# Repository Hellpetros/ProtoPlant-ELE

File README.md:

View this project on [CADLAB.io](https://cadlab.io/project/22799). 

# ProtoPlant-HW

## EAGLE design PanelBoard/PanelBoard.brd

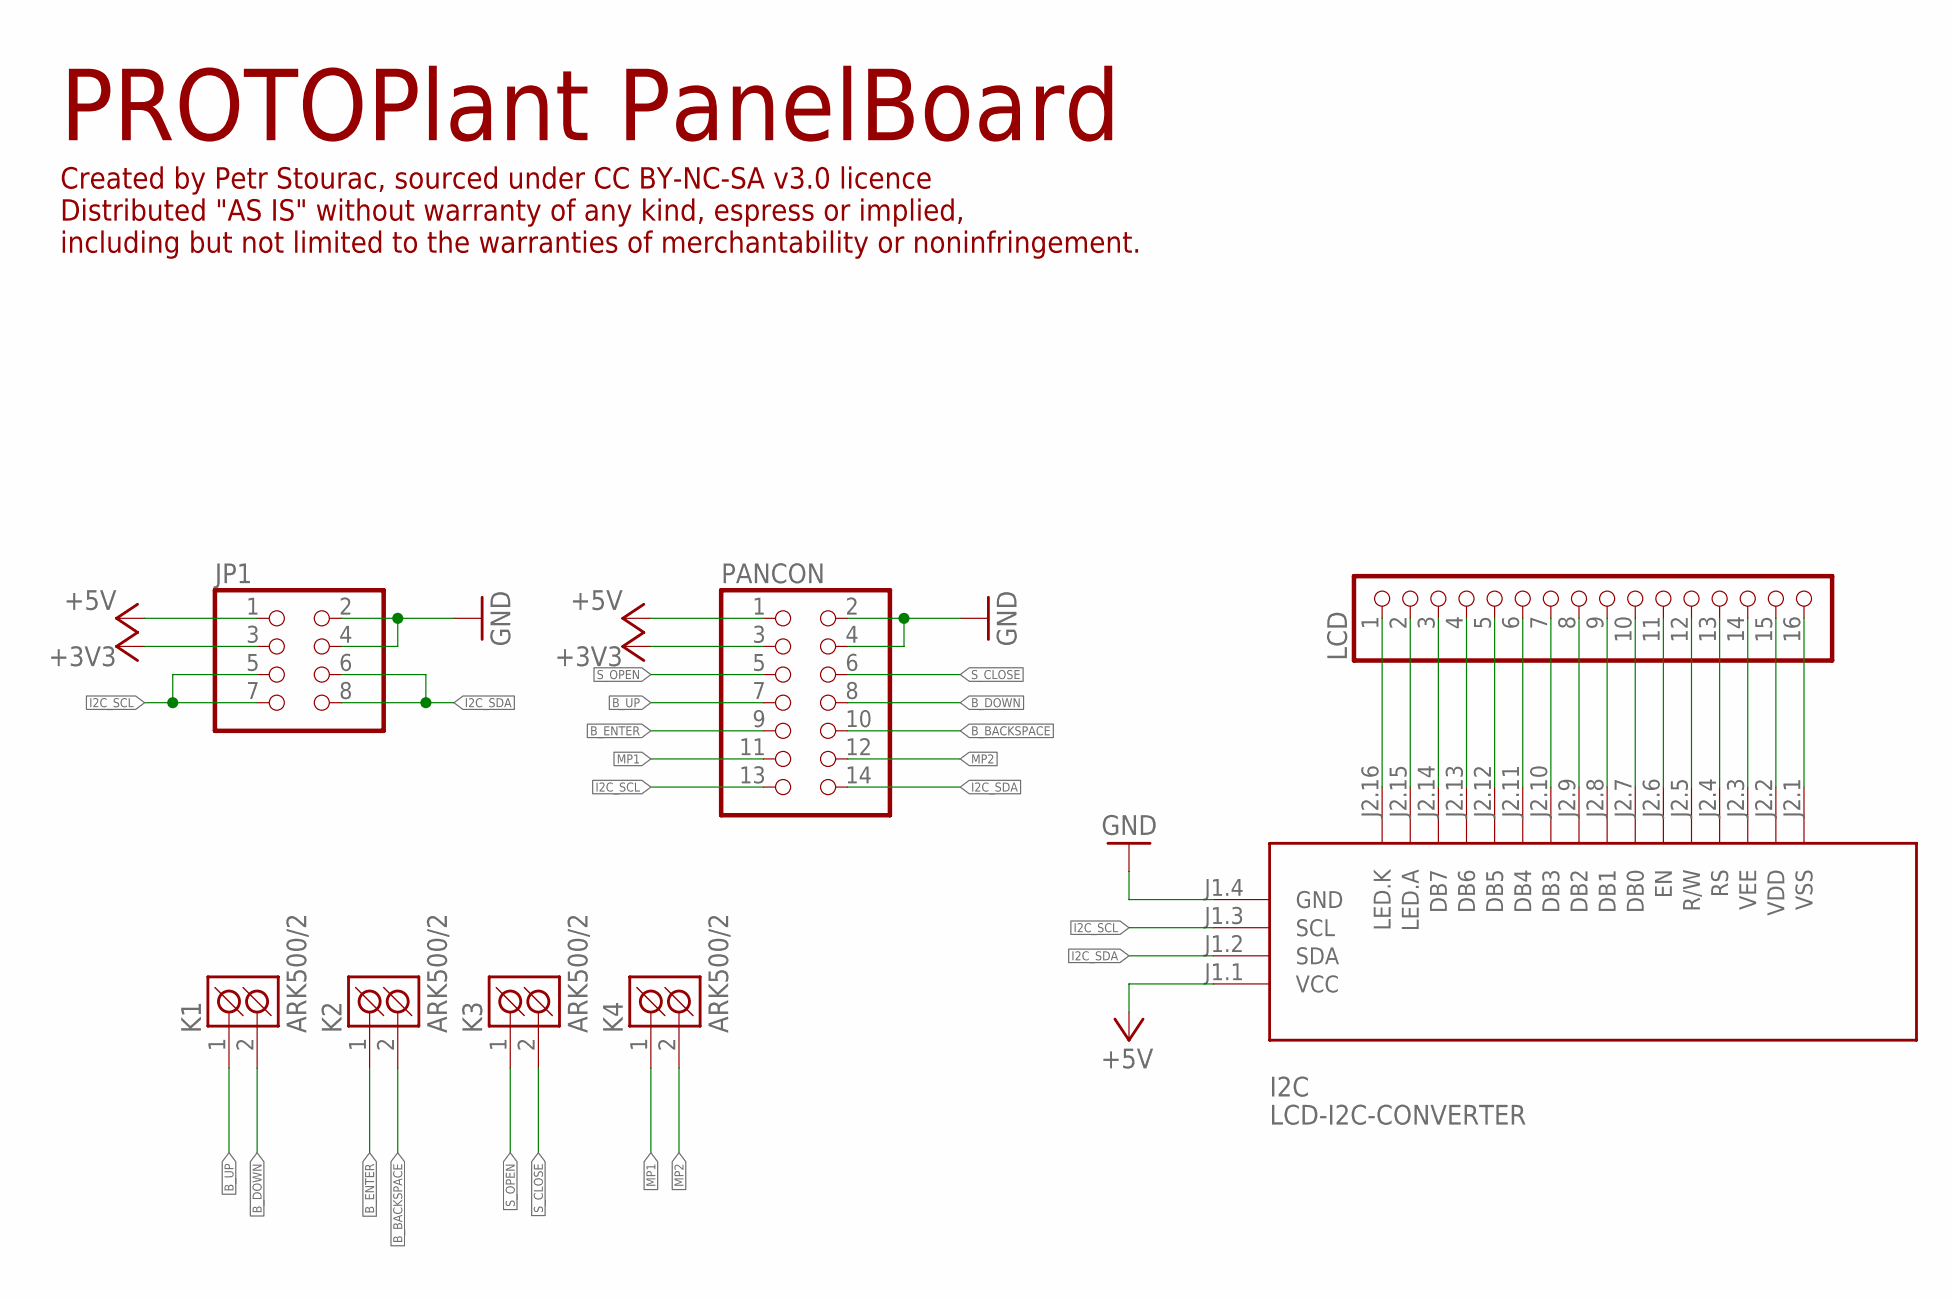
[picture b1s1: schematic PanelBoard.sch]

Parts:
I2C: LCD-I2C-CONVERTER
JP1: PINHD-2X4/90; 2X04/90
K1, K2, K3, K4: ARK500/2
LCD: PINHD-1X16; 1X16
PANCON: PINHD-2X7/90; 2X07/90

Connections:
+3V3: JP1.3, PANCON.3
+5V: I2C.J1.1 (VCC), JP1.1, PANCON.1
B_BACKSPACE: K2.2 (K2), PANCON.10
B_DOWN: K1.2 (K2), PANCON.8
B_ENTER: K2.1 (K1), PANCON.9
B_UP: K1.1 (K1), PANCON.7
GND: I2C.J1.4 (GND), JP1.2, JP1.4, PANCON.2, PANCON.4
I2C_SCL: I2C.J1.3 (SCL), JP1.5, JP1.7, PANCON.13
I2C_SDA: I2C.J1.2 (SDA), JP1.6, JP1.8, PANCON.14
MP1: K4.1 (K1), PANCON.11
MP2: K4.2 (K2), PANCON.12
unnamed: I2C.J2.16 (LED.K), LCD.1
unnamed: I2C.J2.15 (LED.A), LCD.2
unnamed: I2C.J2.14 (DB7), LCD.3
unnamed: I2C.J2.13 (DB6), LCD.4
unnamed: I2C.J2.12 (DB5), LCD.5
unnamed: I2C.J2.11 (DB4), LCD.6
unnamed: I2C.J2.10 (DB3), LCD.7
unnamed: I2C.J2.9 (DB2), LCD.8
unnamed: I2C.J2.8 (DB1), LCD.9
unnamed: I2C.J2.7 (DB0), LCD.10
unnamed: I2C.J2.6 (EN), LCD.11
unnamed: I2C.J2.5 (R/W), LCD.12
unnamed: I2C.J2.4 (RS), LCD.13
unnamed: I2C.J2.3 (VEE), LCD.14
unnamed: I2C.J2.2 (VDD), LCD.15
unnamed: I2C.J2.1 (VSS), LCD.16
S_CLOSE: K3.2 (K2), PANCON.6
S_OPEN: K3.1 (K1), PANCON.5

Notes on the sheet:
PROTOPlant PanelBoard
Created by Petr Stourac, sourced under CC BY-NC-SA v3.0 licence Distributed "AS IS" without warranty of any kind, espress or implied, including but not limited to the warranties of merchantability or noninfringement.

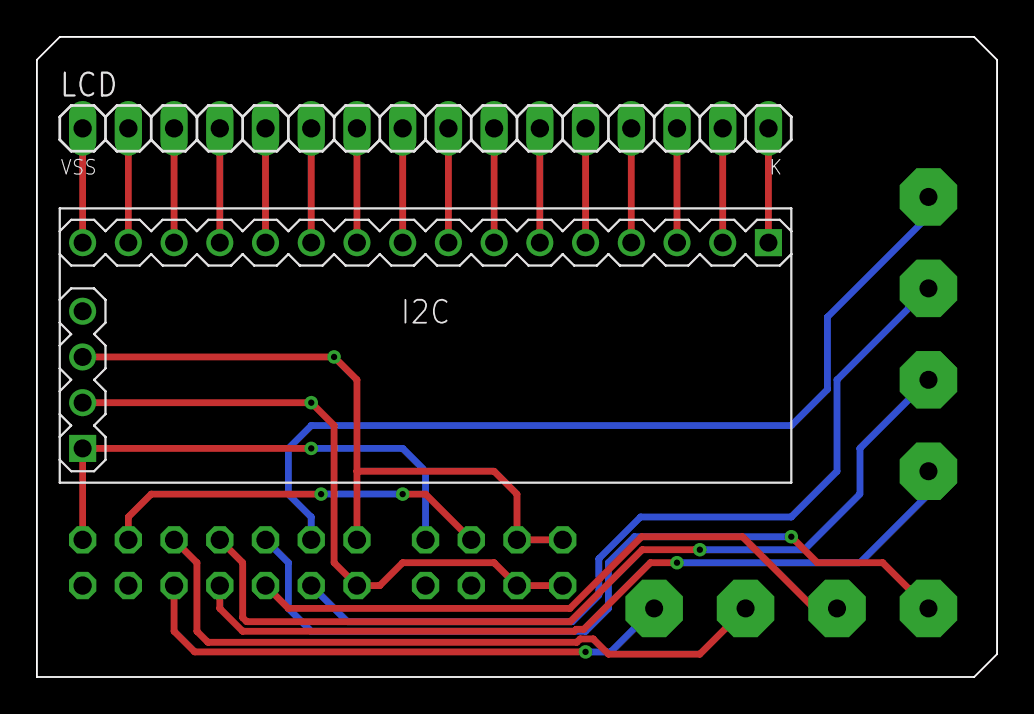
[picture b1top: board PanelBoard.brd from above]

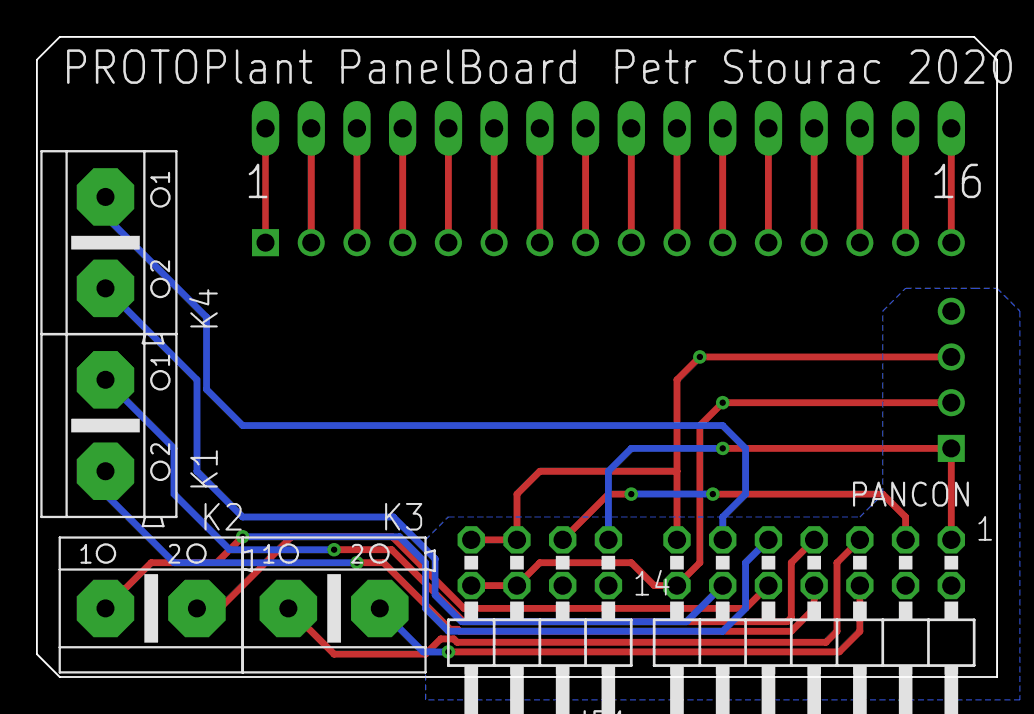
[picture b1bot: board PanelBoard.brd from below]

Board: 2 copper layers, 53.3 x 35.6 mm, 8 parts (6 on the bottom side), 29 nets.

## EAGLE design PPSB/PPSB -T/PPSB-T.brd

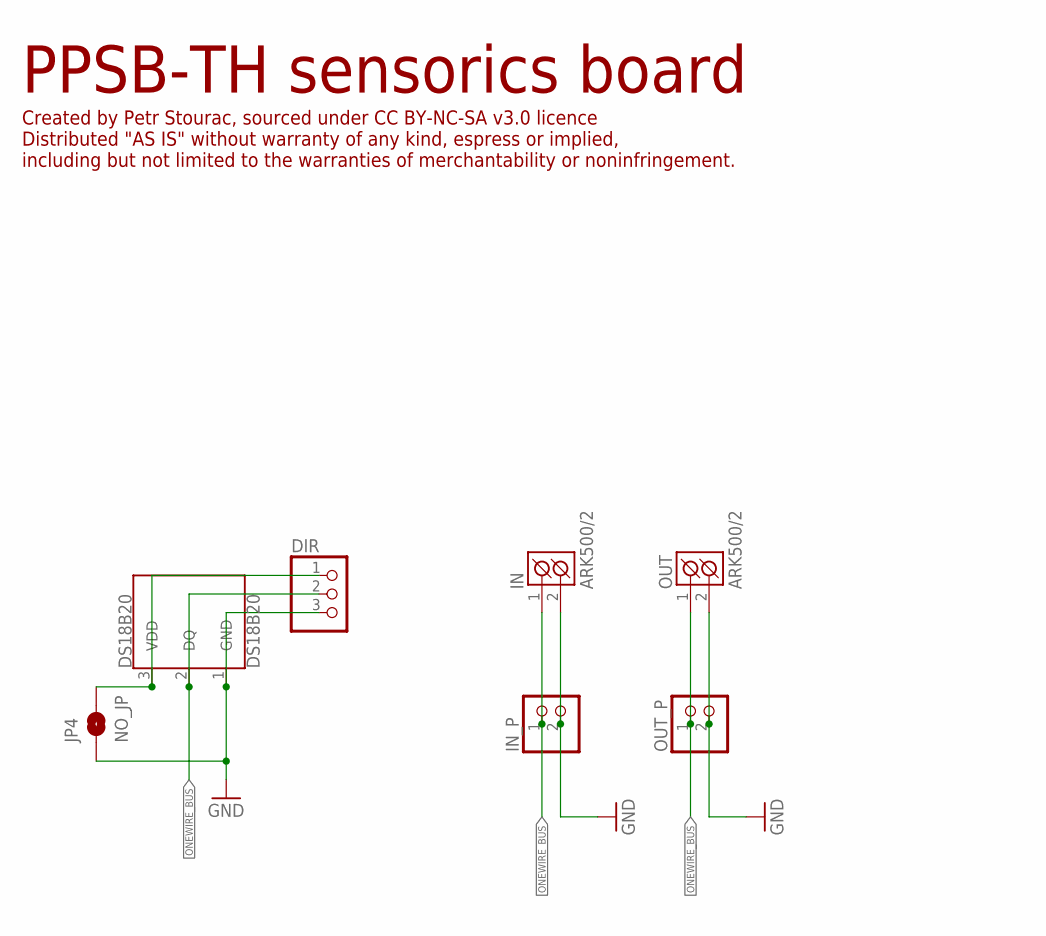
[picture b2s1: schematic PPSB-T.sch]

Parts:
DIR: PINHD-1X3; 1X03
DS18B20: DS18B20; TO-92-AMMO
IN: ARK500/2
IN_P: PINHD-1X2; 1X02
JP4: NO_JP; SMT-JUMPER_2_NO_NO-SILK
OUT: ARK500/2
OUT_P: PINHD-1X2; 1X02

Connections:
GND: DIR.3, DS18B20.1 (GND), IN.2 (K2), IN_P.2, JP4.1, OUT.2 (K2), OUT_P.2
unnamed: DIR.1, DS18B20.3 (VDD), JP4.2
ONEWIRE_BUS: DIR.2, DS18B20.2 (DQ), IN.1 (K1), IN_P.1, OUT.1 (K1), OUT_P.1

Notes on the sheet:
PPSB-TH sensorics board
Created by Petr Stourac, sourced under CC BY-NC-SA v3.0 licence Distributed "AS IS" without warranty of any kind, espress or implied, including but not limited to the warranties of merchantability or noninfringement.

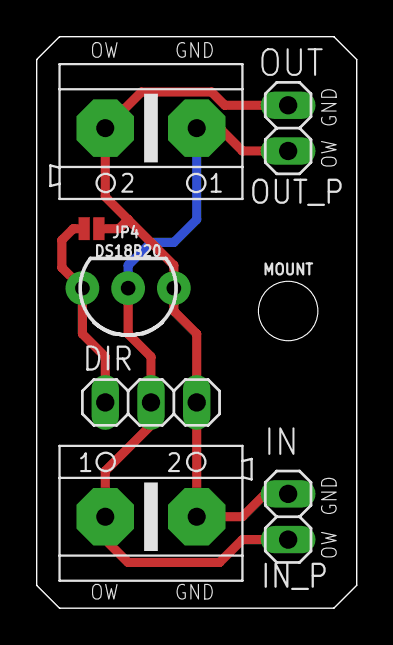
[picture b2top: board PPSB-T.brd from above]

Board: 2 copper layers, 17.8 x 31.8 mm, 8 parts (0 on the bottom side), 3 nets.

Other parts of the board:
MOUNT: STAND-OFF

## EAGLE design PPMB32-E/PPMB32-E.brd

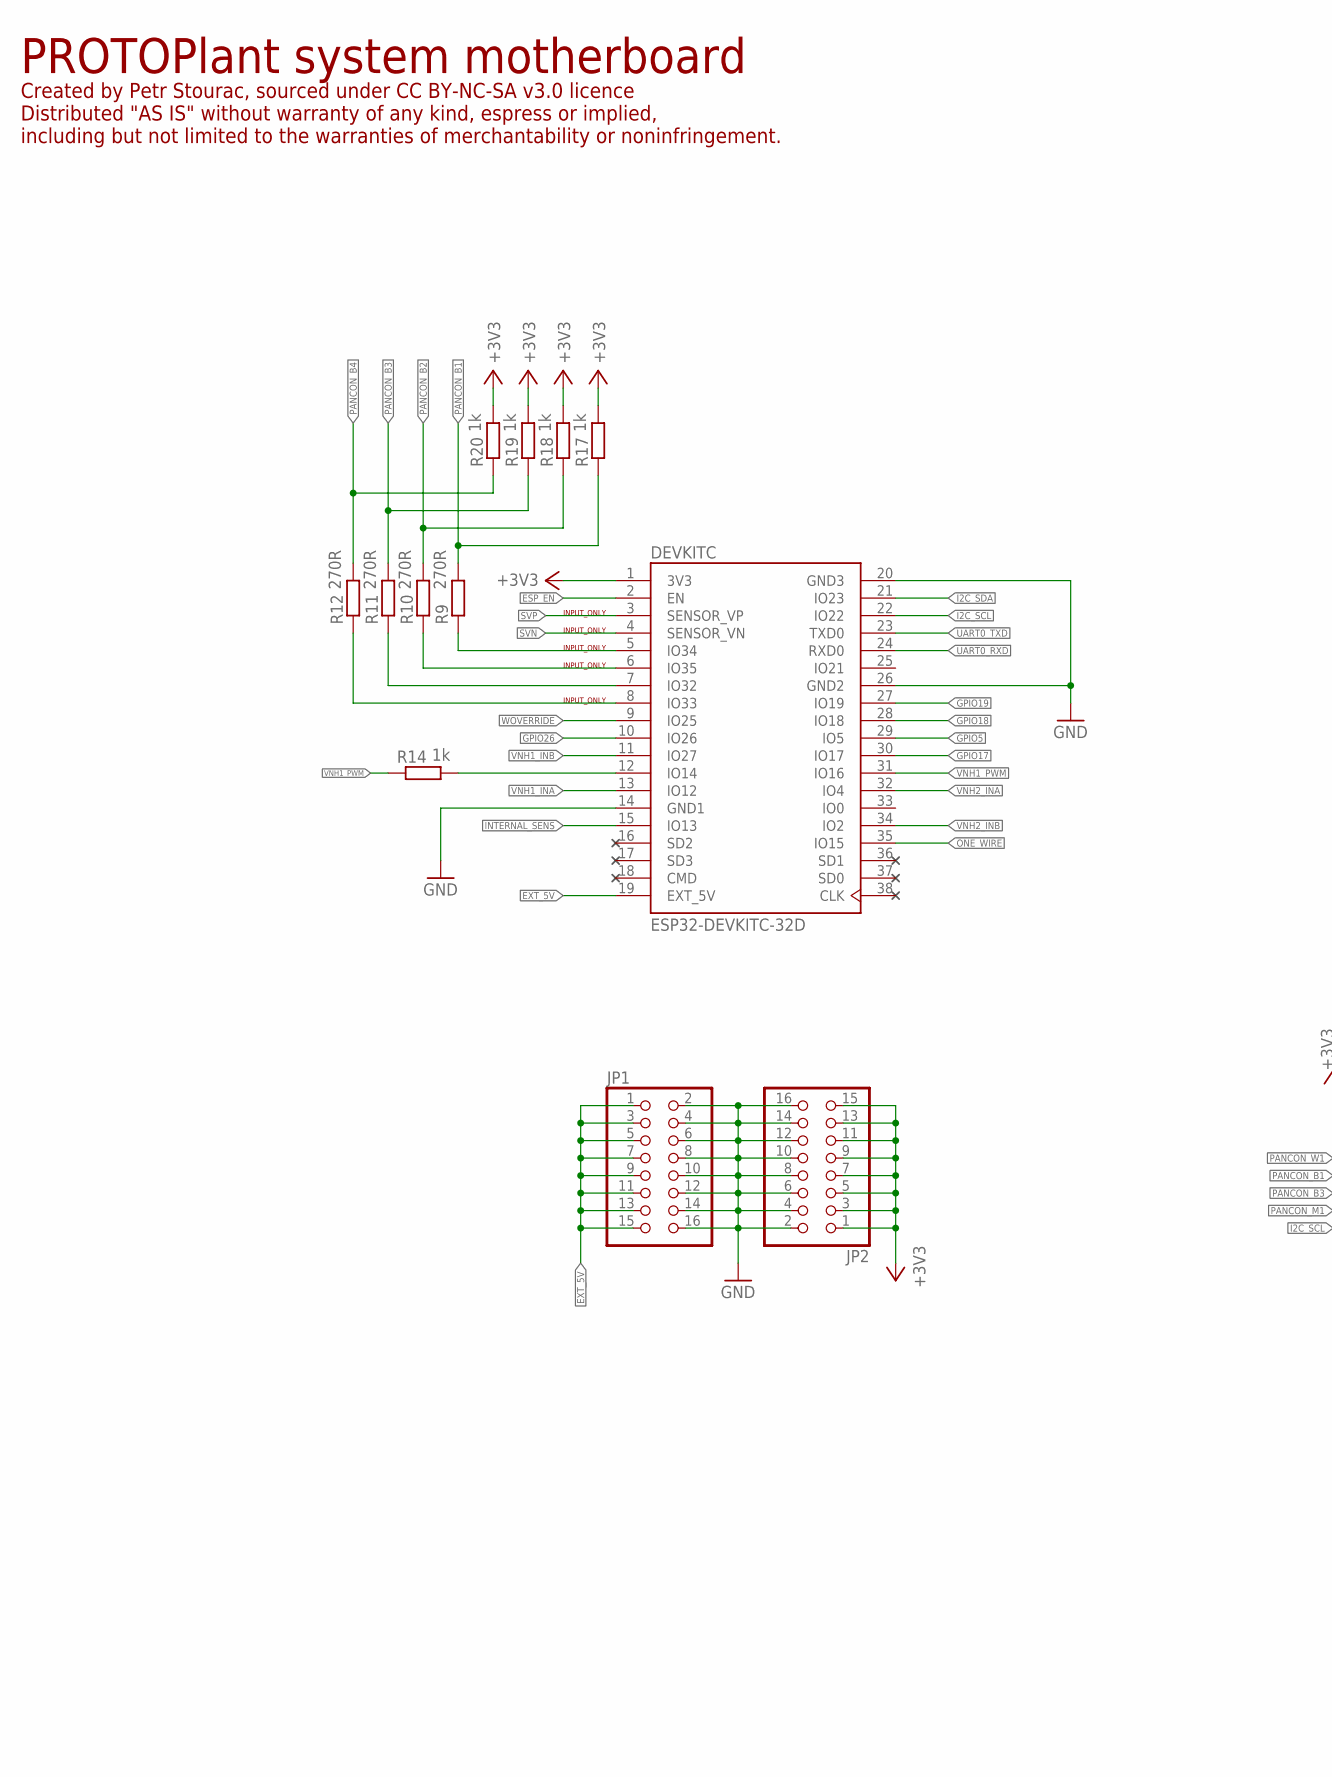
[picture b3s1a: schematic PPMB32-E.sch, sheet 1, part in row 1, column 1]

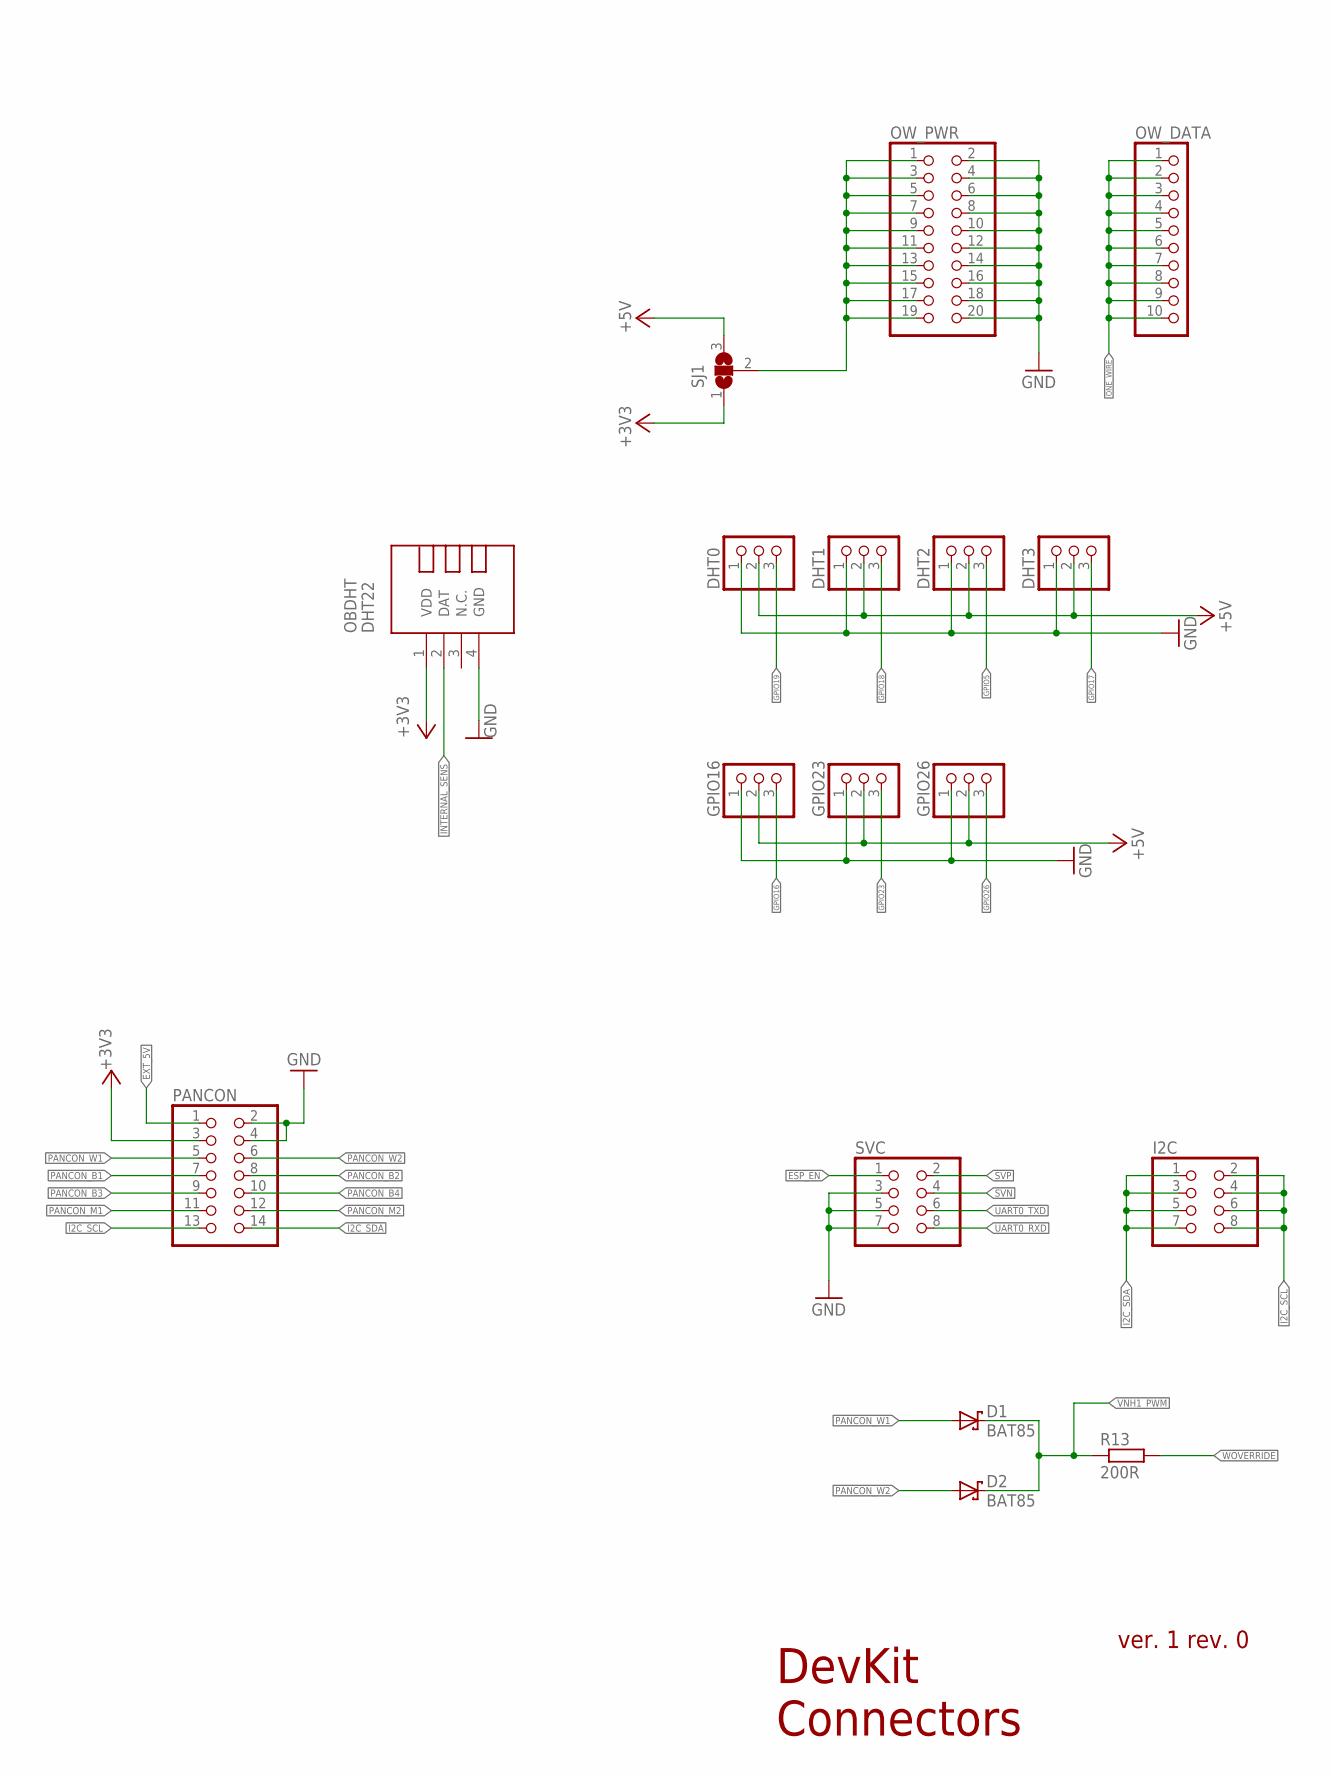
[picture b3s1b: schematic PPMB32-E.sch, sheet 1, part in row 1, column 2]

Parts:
D1, D2: BAT85; DO35-7
DEVKITC: ESP32-DEVKITC-32D; MODULE_ESP32-DEVKITC-32D
DHT0, DHT1, DHT2, DHT3: PINHD-1X3; 1X03
GPIO16, GPIO23, GPIO26: PINHD-1X3; 1X03
I2C: PINHD-2X4; 2X04
JP1, JP2: PINHD-2X8; 2X08
OBDHT: DHT22; TEMP-HUM-SENSOR-DHT22
OW_DATA: PINHD-1X10; 1X10
OW_PWR: PINHD-2X10; 2X10
PANCON: PINHD-2X7; 2X07
R9, R10, R11, R12: 270R; R0603
R13: 200R; R0603
R14, R17, R18, R19, R20: 1k; R0603
SJ1: SJ2W; SJ_2
SVC: PINHD-2X4; 2X04

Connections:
+3V3: DEVKITC.1 (3V3), JP2.1, JP2.3, JP2.5, JP2.7, JP2.9, JP2.11, JP2.13, JP2.15, OBDHT.1 (VDD), PANCON.3, R17.2, R18.2, R19.2, R20.2, SJ1.1; also elsewhere on the board
+5V: DHT0.2, DHT1.2, DHT2.2, DHT3.2, GPIO16.2, GPIO23.2, GPIO26.2, SJ1.3
ESP_EN: DEVKITC.2 (EN), SVC.1
EXT_5V: DEVKITC.19 (EXT_5V), JP1.1, JP1.3, JP1.5, JP1.7, JP1.9, JP1.11, JP1.13, JP1.15, PANCON.1; also elsewhere on the board
GND: DEVKITC.14 (GND1), DEVKITC.20 (GND3), DEVKITC.26 (GND2), DHT0.1, DHT1.1, DHT2.1, DHT3.1, GPIO16.1, GPIO23.1, GPIO26.1, JP1.2, JP1.4, JP1.6, JP1.8, JP1.10, JP1.12, JP1.14, JP1.16, JP2.2, JP2.4, JP2.6, JP2.8, JP2.10, JP2.12, JP2.14, JP2.16, OBDHT.4 (GND), OW_PWR.2, OW_PWR.4, OW_PWR.6, OW_PWR.8, OW_PWR.10, OW_PWR.12, OW_PWR.14, OW_PWR.16, OW_PWR.18, OW_PWR.20, PANCON.2, PANCON.4, SVC.3, SVC.5, SVC.7; also elsewhere on the board
GPIO5: DEVKITC.29 (IO5), DHT2.3
GPIO16: GPIO16.3
GPIO17: DEVKITC.30 (IO17), DHT3.3
GPIO18: DEVKITC.28 (IO18), DHT1.3
GPIO19: DEVKITC.27 (IO19), DHT0.3
GPIO23: GPIO23.3
GPIO26: DEVKITC.10 (IO26), GPIO26.3
I2C_SCL: DEVKITC.22 (IO22), I2C.2, I2C.4, I2C.6, I2C.8, PANCON.13
I2C_SDA: DEVKITC.21 (IO23), I2C.1, I2C.3, I2C.5, I2C.7, PANCON.14
INTERNAL_SENS: DEVKITC.15 (IO13), OBDHT.2 (DAT)
unnamed: DEVKITC.5 (IO34), R9.1
unnamed: DEVKITC.6 (IO35), R10.1
unnamed: DEVKITC.7 (IO32), R11.1
unnamed: DEVKITC.8 (IO33), R12.1
unnamed: OW_PWR.1, OW_PWR.3, OW_PWR.5, OW_PWR.7, OW_PWR.9, OW_PWR.11, OW_PWR.13, OW_PWR.15, OW_PWR.17, OW_PWR.19, SJ1.2
unnamed: DEVKITC.12 (IO14), R14.2
ONE_WIRE: DEVKITC.35 (IO15), OW_DATA.1, OW_DATA.2, OW_DATA.3, OW_DATA.4, OW_DATA.5, OW_DATA.6, OW_DATA.7, OW_DATA.8, OW_DATA.9, OW_DATA.10
PANCON_B1: PANCON.7, R9.2, R17.1
PANCON_B2: PANCON.8, R10.2, R18.1
PANCON_B3: PANCON.9, R11.2, R19.1
PANCON_B4: PANCON.10, R12.2, R20.1
PANCON_M1: PANCON.11
PANCON_M2: PANCON.12
PANCON_W1: D1.A, PANCON.5; also elsewhere on the board
PANCON_W2: D2.A, PANCON.6; also elsewhere on the board
SVN: DEVKITC.4 (SENSOR_VN), SVC.4
SVP: DEVKITC.3 (SENSOR_VP), SVC.2
UART0_RXD: DEVKITC.24 (RXD0), SVC.8
UART0_TXD: DEVKITC.23 (TXD0), SVC.6
VNH1_INA: DEVKITC.13 (IO12); also elsewhere on the board
VNH1_INB: DEVKITC.11 (IO27); also elsewhere on the board
VNH1_PWM: D1.C, D2.C, DEVKITC.31 (IO16), R13.1, R14.1; also elsewhere on the board
VNH2_INA: DEVKITC.32 (IO4); also elsewhere on the board
VNH2_INB: DEVKITC.34 (IO2); also elsewhere on the board
WOVERRIDE: DEVKITC.9 (IO25), R13.2

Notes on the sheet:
DevKit Connectors
INPUT_ONLY
ver. 1 rev. 0
PROTOPlant system motherboard
Created by Petr Stourac, sourced under CC BY-NC-SA v3.0 licence Distributed "AS IS" without warranty of any kind, espress or implied, including but not limited to the warranties of merchantability or noninfringement.

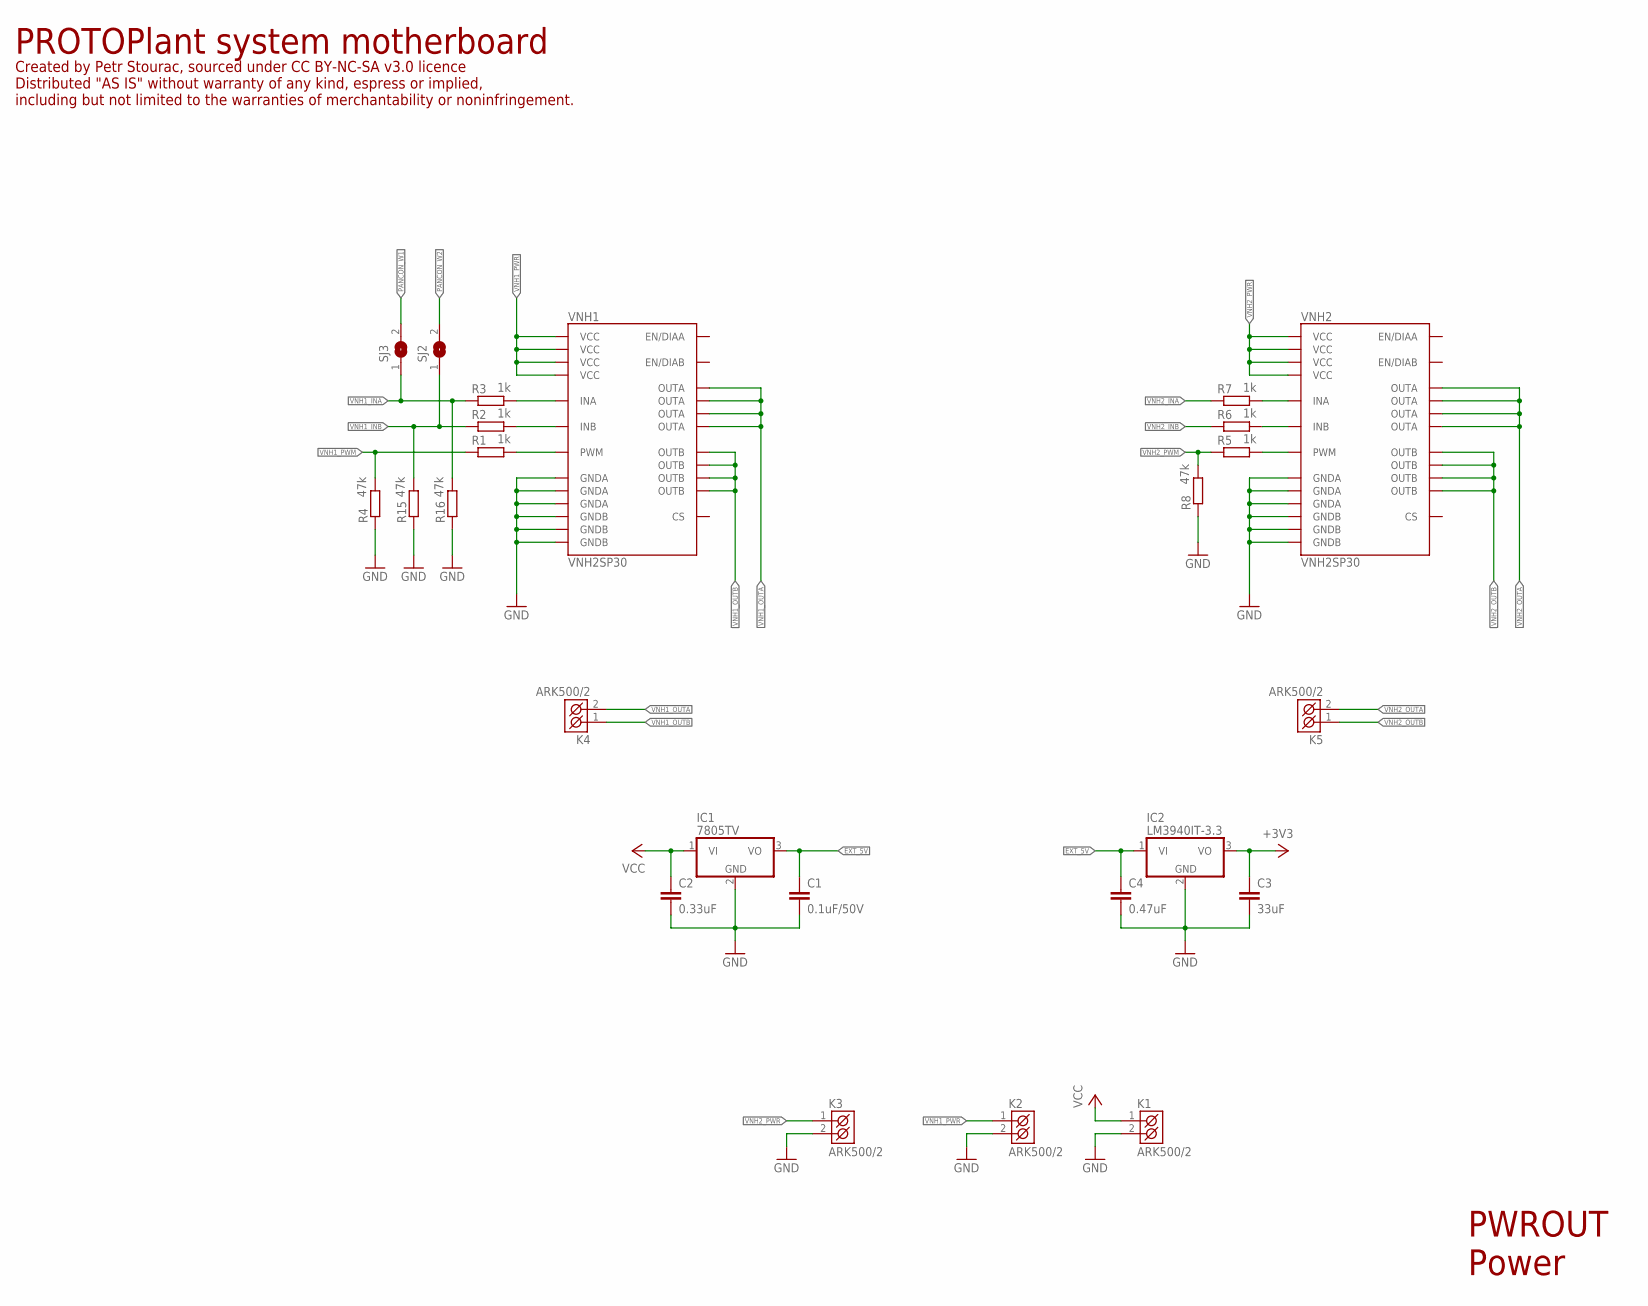
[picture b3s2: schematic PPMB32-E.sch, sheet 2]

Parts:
C1: 0.1uF/50V; C1206K
C2: 0.33uF; C1206K
C3: 33uF; C1206K
C4: 0.47uF; C1206K
IC1: 7805TV; TO220V
IC2: LM3940IT-3.3; TO220V
K1, K2, K3, K4, K5: ARK500/2
R1, R2, R3, R5, R6, R7: 1k; R0603
R4, R8, R15, R16: 47k; R0603
SJ2, SJ3: SJ
VNH1, VNH2: VNH2SP30

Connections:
+3V3: C3.1, IC2.3 (VO); also elsewhere on the board
EXT_5V: C1.1, C4.1, IC1.3 (VO), IC2.1 (VI); also elsewhere on the board
GND: C1.2, C2.2, C3.2, C4.2, IC1.2 (GND), IC2.2 (GND), K1.2 (K2), K2.2 (K2), K3.2 (K2), R4.1, R8.1, R15.1, R16.1, VNH1.18 (GNDB), VNH1.19 (GNDB), VNH1.20 (GNDB), VNH1.26 (GNDA), VNH1.27 (GNDA), VNH1.28 (GNDA), VNH2.18 (GNDB), VNH2.19 (GNDB), VNH2.20 (GNDB), VNH2.26 (GNDA), VNH2.27 (GNDA), VNH2.28 (GNDA); also elsewhere on the board
unnamed: R3.2, VNH1.5 (INA)
unnamed: R2.2, VNH1.11 (INB)
unnamed: R1.2, VNH1.8 (PWM)
unnamed: R5.2, VNH2.8 (PWM)
unnamed: R6.2, VNH2.11 (INB)
unnamed: R7.2, VNH2.5 (INA)
PANCON_W1: SJ3.2; also elsewhere on the board
PANCON_W2: SJ2.2; also elsewhere on the board
VCC: C2.1, IC1.1 (VI), K1.1 (K1)
VNH1_INA: R3.1, R16.2, SJ3.1; also elsewhere on the board
VNH1_INB: R2.1, R15.2, SJ2.1; also elsewhere on the board
VNH1_OUTA: K4.2 (K2), VNH1.1 (OUTA), VNH1.25 (OUTA), VNH1.30 (OUTA), VNH1.SLUG3 (OUTA)
VNH1_OUTB: K4.1 (K1), VNH1.15 (OUTB), VNH1.16 (OUTB), VNH1.21 (OUTB), VNH1.SLUG2 (OUTB)
VNH1_PWM: R1.1, R4.2; also elsewhere on the board
VNH1_PWR: K2.1 (K1), VNH1.3 (VCC), VNH1.13 (VCC), VNH1.23 (VCC), VNH1.SLUG1 (VCC)
VNH2_INA: R7.1; also elsewhere on the board
VNH2_INB: R6.1; also elsewhere on the board
VNH2_OUTA: K5.2 (K2), VNH2.1 (OUTA), VNH2.25 (OUTA), VNH2.30 (OUTA), VNH2.SLUG3 (OUTA)
VNH2_OUTB: K5.1 (K1), VNH2.15 (OUTB), VNH2.16 (OUTB), VNH2.21 (OUTB), VNH2.SLUG2 (OUTB)
VNH2_PWM: R5.1, R8.2
VNH2_PWR: K3.1 (K1), VNH2.3 (VCC), VNH2.13 (VCC), VNH2.23 (VCC), VNH2.SLUG1 (VCC)

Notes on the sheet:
PWROUT Power
PROTOPlant system motherboard
Created by Petr Stourac, sourced under CC BY-NC-SA v3.0 licence Distributed "AS IS" without warranty of any kind, espress or implied, including but not limited to the warranties of merchantability or noninfringement.

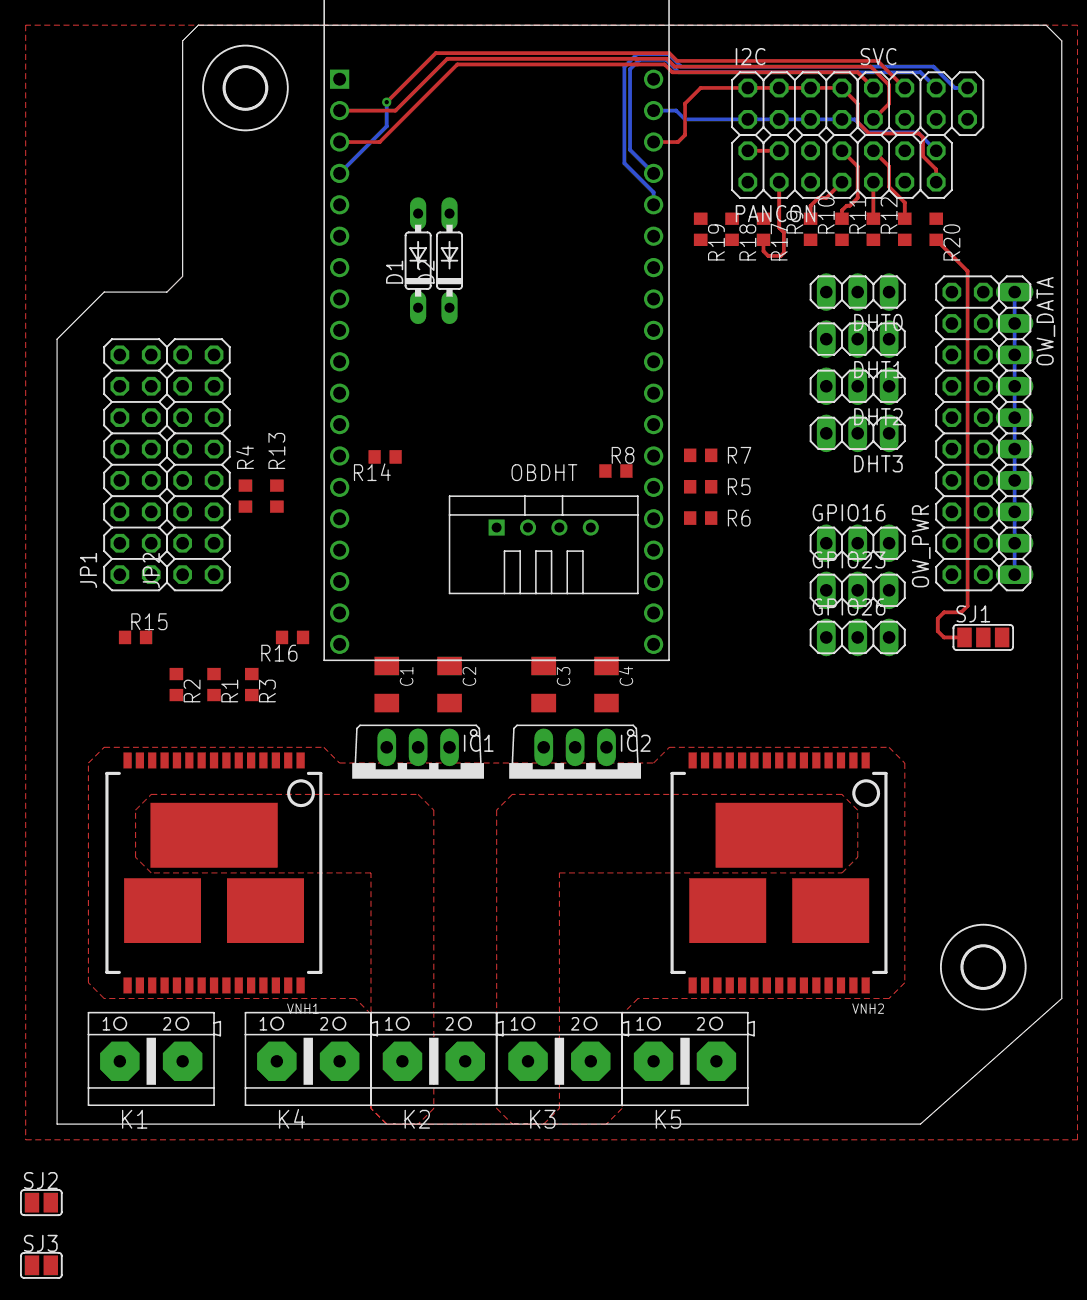
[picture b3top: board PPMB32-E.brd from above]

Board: 2 copper layers, 81.3 x 88.9 mm, 56 parts (0 on the bottom side), 50 nets.

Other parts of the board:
U$7, U$8: 3,3

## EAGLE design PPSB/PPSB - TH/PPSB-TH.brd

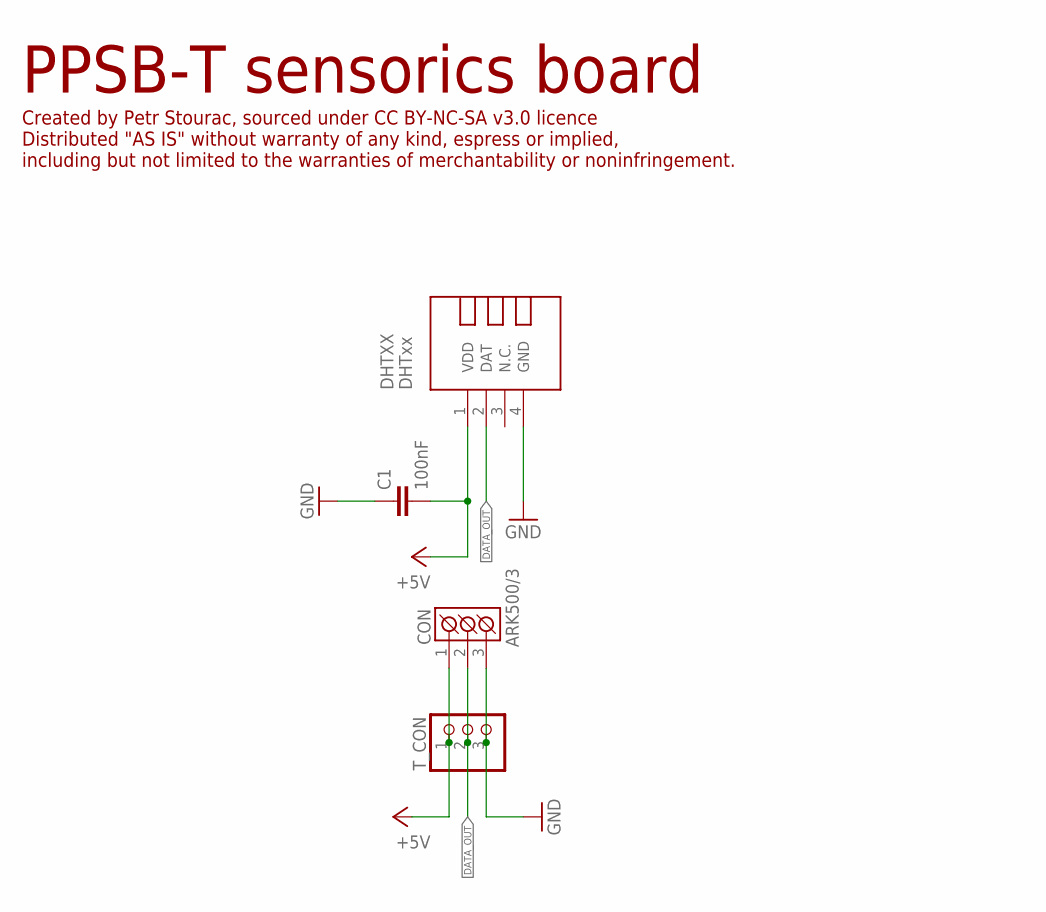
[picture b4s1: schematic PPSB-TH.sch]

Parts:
C1: 100nF; C0603
CON: ARK500/3
DHTXX: DHTxx; TEMP-HUM-SENSOR-DHT22
T_CON: PINHD-1X3; 1X03

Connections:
+5V: C1.2, CON.1 (K1), DHTXX.1 (VDD), T_CON.1
DATA_OUT: CON.2 (K2), DHTXX.2 (DAT), T_CON.2
GND: C1.1, CON.3 (K3), DHTXX.4 (GND), T_CON.3

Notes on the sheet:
PPSB-T sensorics board
Created by Petr Stourac, sourced under CC BY-NC-SA v3.0 licence Distributed "AS IS" without warranty of any kind, espress or implied, including but not limited to the warranties of merchantability or noninfringement.

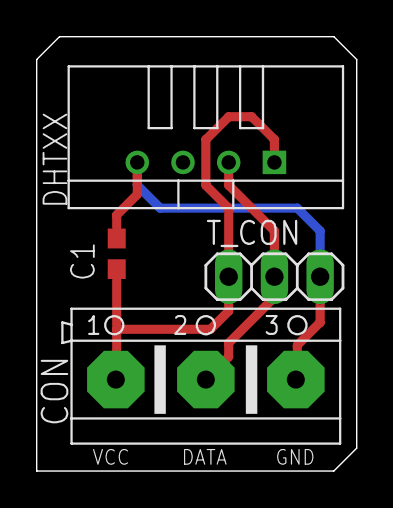
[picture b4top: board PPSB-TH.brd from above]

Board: 2 copper layers, 17.8 x 24.1 mm, 4 parts (0 on the bottom side), 3 nets.

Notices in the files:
parts and their libraries:
diy-modules: Released under the Creative Commons Attribution 4.0 International License: http://creativecommons.org/licenses/by/4.0
Copyright (C) PaJa 2011-2014
SparkFun-IC-Special-Function: Licensing: Creative Commons ShareAlike 4.0 International - https://creativecommons.org/licenses/by-sa/4.0
